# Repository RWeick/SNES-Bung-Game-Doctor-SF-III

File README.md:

# SNES-Bung-Game-Doctor-SF-III
The mainboard and memory board addon Kicad files for the Bung Game Doctor SF III. 

There were two bodged capacitors, 30 pF and 100 pF, that I've added footprints for on the PCB. I have also added a PLCC-32 footprint for the ROM. Everything else is original.

Mainboard PCB Thickness: 1.6 mm
RAM PCB Thicknesses: 1.2 mm

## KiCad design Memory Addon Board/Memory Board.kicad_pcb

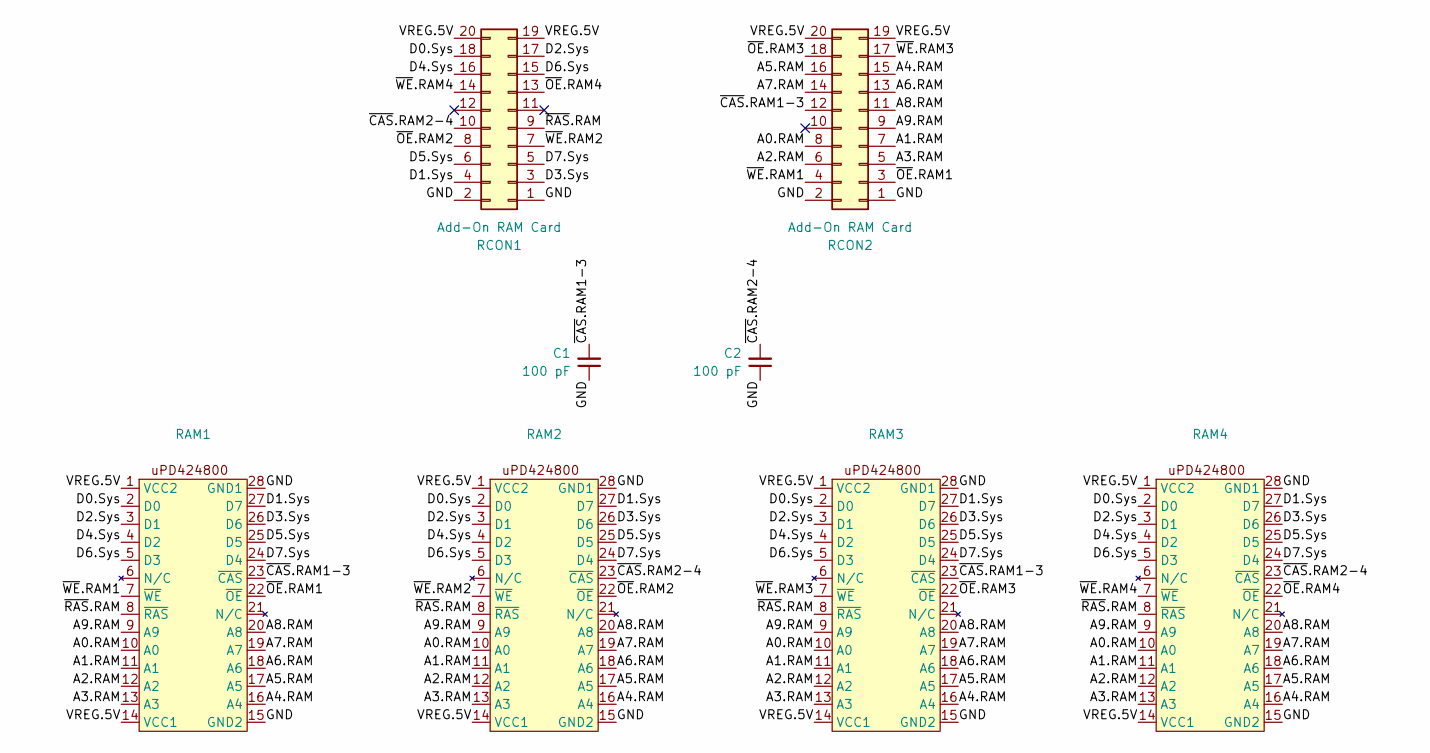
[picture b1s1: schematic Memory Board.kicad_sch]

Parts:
C1, C2: 100 pF; SMD Passive
RAM1, RAM2, RAM3, RAM4: uPD424800
RCON1, RCON2: Add-On RAM Card; PinHeader_2x10_P2.54mm_Vertical

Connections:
/A0.RAM: RAM1.10 (A0), RAM2.10 (A0), RAM3.10 (A0), RAM4.10 (A0), RCON2.8
/A1.RAM: RAM1.11 (A1), RAM2.11 (A1), RAM3.11 (A1), RAM4.11 (A1), RCON2.7
/A2.RAM: RAM1.12 (A2), RAM2.12 (A2), RAM3.12 (A2), RAM4.12 (A2), RCON2.6
/A3.RAM: RAM1.13 (A3), RAM2.13 (A3), RAM3.13 (A3), RAM4.13 (A3), RCON2.5
/A4.RAM: RAM1.16 (A4), RAM2.16 (A4), RAM3.16 (A4), RAM4.16 (A4), RCON2.15
/A5.RAM: RAM1.17 (A5), RAM2.17 (A5), RAM3.17 (A5), RAM4.17 (A5), RCON2.16
/A6.RAM: RAM1.18 (A6), RAM2.18 (A6), RAM3.18 (A6), RAM4.18 (A6), RCON2.13
/A7.RAM: RAM1.19 (A7), RAM2.19 (A7), RAM3.19 (A7), RAM4.19 (A7), RCON2.14
/A8.RAM: RAM1.20 (A8), RAM2.20 (A8), RAM3.20 (A8), RAM4.20 (A8), RCON2.11
/A9.RAM: RAM1.9 (A9), RAM2.9 (A9), RAM3.9 (A9), RAM4.9 (A9), RCON2.9
/D0.Sys: RAM1.2 (D0), RAM2.2 (D0), RAM3.2 (D0), RAM4.2 (D0), RCON1.18
/D1.Sys: RAM1.27 (D7), RAM2.27 (D7), RAM3.27 (D7), RAM4.27 (D7), RCON1.4
/D2.Sys: RAM1.3 (D1), RAM2.3 (D1), RAM3.3 (D1), RAM4.3 (D1), RCON1.17
/D3.Sys: RAM1.26 (D6), RAM2.26 (D6), RAM3.26 (D6), RAM4.26 (D6), RCON1.3
/D4.Sys: RAM1.4 (D2), RAM2.4 (D2), RAM3.4 (D2), RAM4.4 (D2), RCON1.16
/D5.Sys: RAM1.25 (D5), RAM2.25 (D5), RAM3.25 (D5), RAM4.25 (D5), RCON1.6
/D6.Sys: RAM1.5 (D3), RAM2.5 (D3), RAM3.5 (D3), RAM4.5 (D3), RCON1.15
/D7.Sys: RAM1.24 (D4), RAM2.24 (D4), RAM3.24 (D4), RAM4.24 (D4), RCON1.5
/GND: C1.1, C2.1, RAM1.15 (GND2), RAM1.28 (GND1), RAM2.15 (GND2), RAM2.28 (GND1), RAM3.15 (GND2), RAM3.28 (GND1), RAM4.15 (GND2), RAM4.28 (GND1), RCON1.1, RCON1.2, RCON2.1, RCON2.2
/VREG.5V: RAM1.1 (VCC2), RAM1.14 (VCC1), RAM2.1 (VCC2), RAM2.14 (VCC1), RAM3.1 (VCC2), RAM3.14 (VCC1), RAM4.1 (VCC2), RAM4.14 (VCC1), RCON1.19, RCON1.20, RCON2.19, RCON2.20
/~CAS.RAM1-3: C1.2, RAM1.23 (~CAS), RAM3.23 (~CAS), RCON2.12
/~CAS.RAM2-4: C2.2, RAM2.23 (~CAS), RAM4.23 (~CAS), RCON1.10
/~OE.RAM1: RAM1.22 (~OE), RCON2.3
/~OE.RAM2: RAM2.22 (~OE), RCON1.8
/~OE.RAM3: RAM3.22 (~OE), RCON2.18
/~OE.RAM4: RAM4.22 (~OE), RCON1.13
/~RAS.RAM: RAM1.8 (~RAS), RAM2.8 (~RAS), RAM3.8 (~RAS), RAM4.8 (~RAS), RCON1.9
/~WE.RAM1: RAM1.7 (~WE), RCON2.4
/~WE.RAM2: RAM2.7 (~WE), RCON1.7
/~WE.RAM3: RAM3.7 (~WE), RCON2.17
/~WE.RAM4: RAM4.7 (~WE), RCON1.14

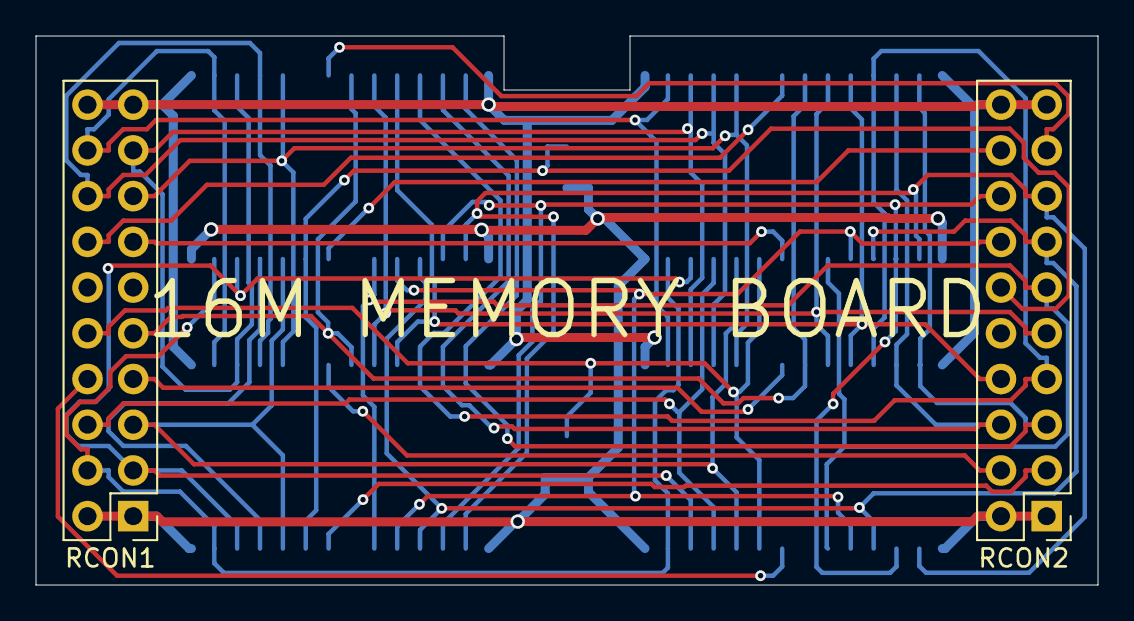
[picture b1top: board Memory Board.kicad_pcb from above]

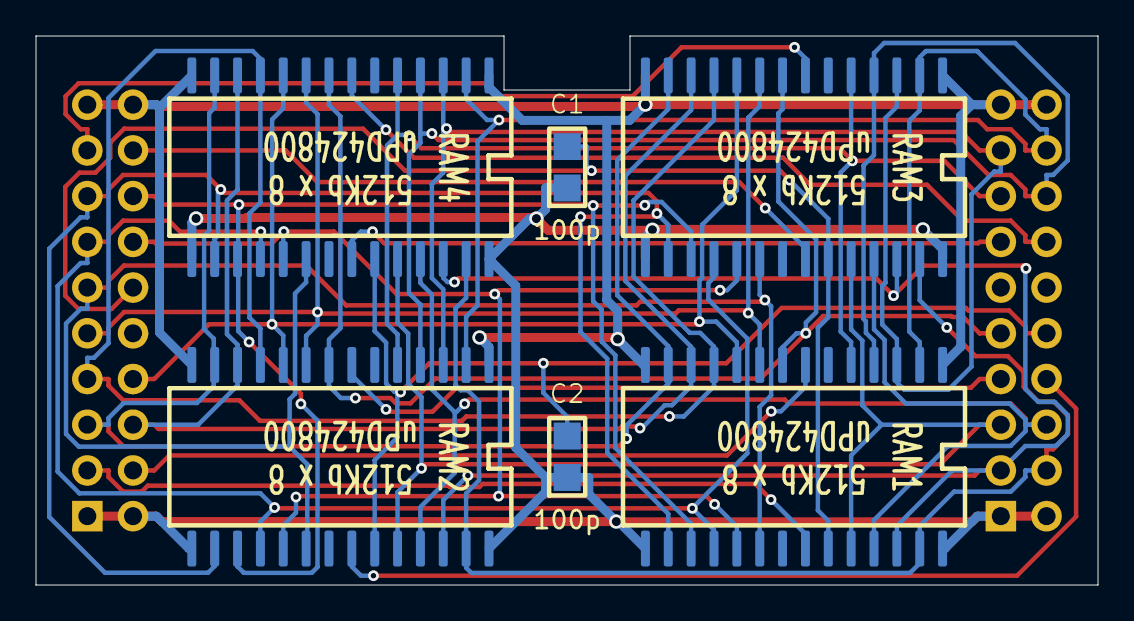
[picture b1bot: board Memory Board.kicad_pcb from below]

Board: 2 copper layers, 59.0 x 30.5 mm, 8 parts (6 on the bottom side), 31 nets.

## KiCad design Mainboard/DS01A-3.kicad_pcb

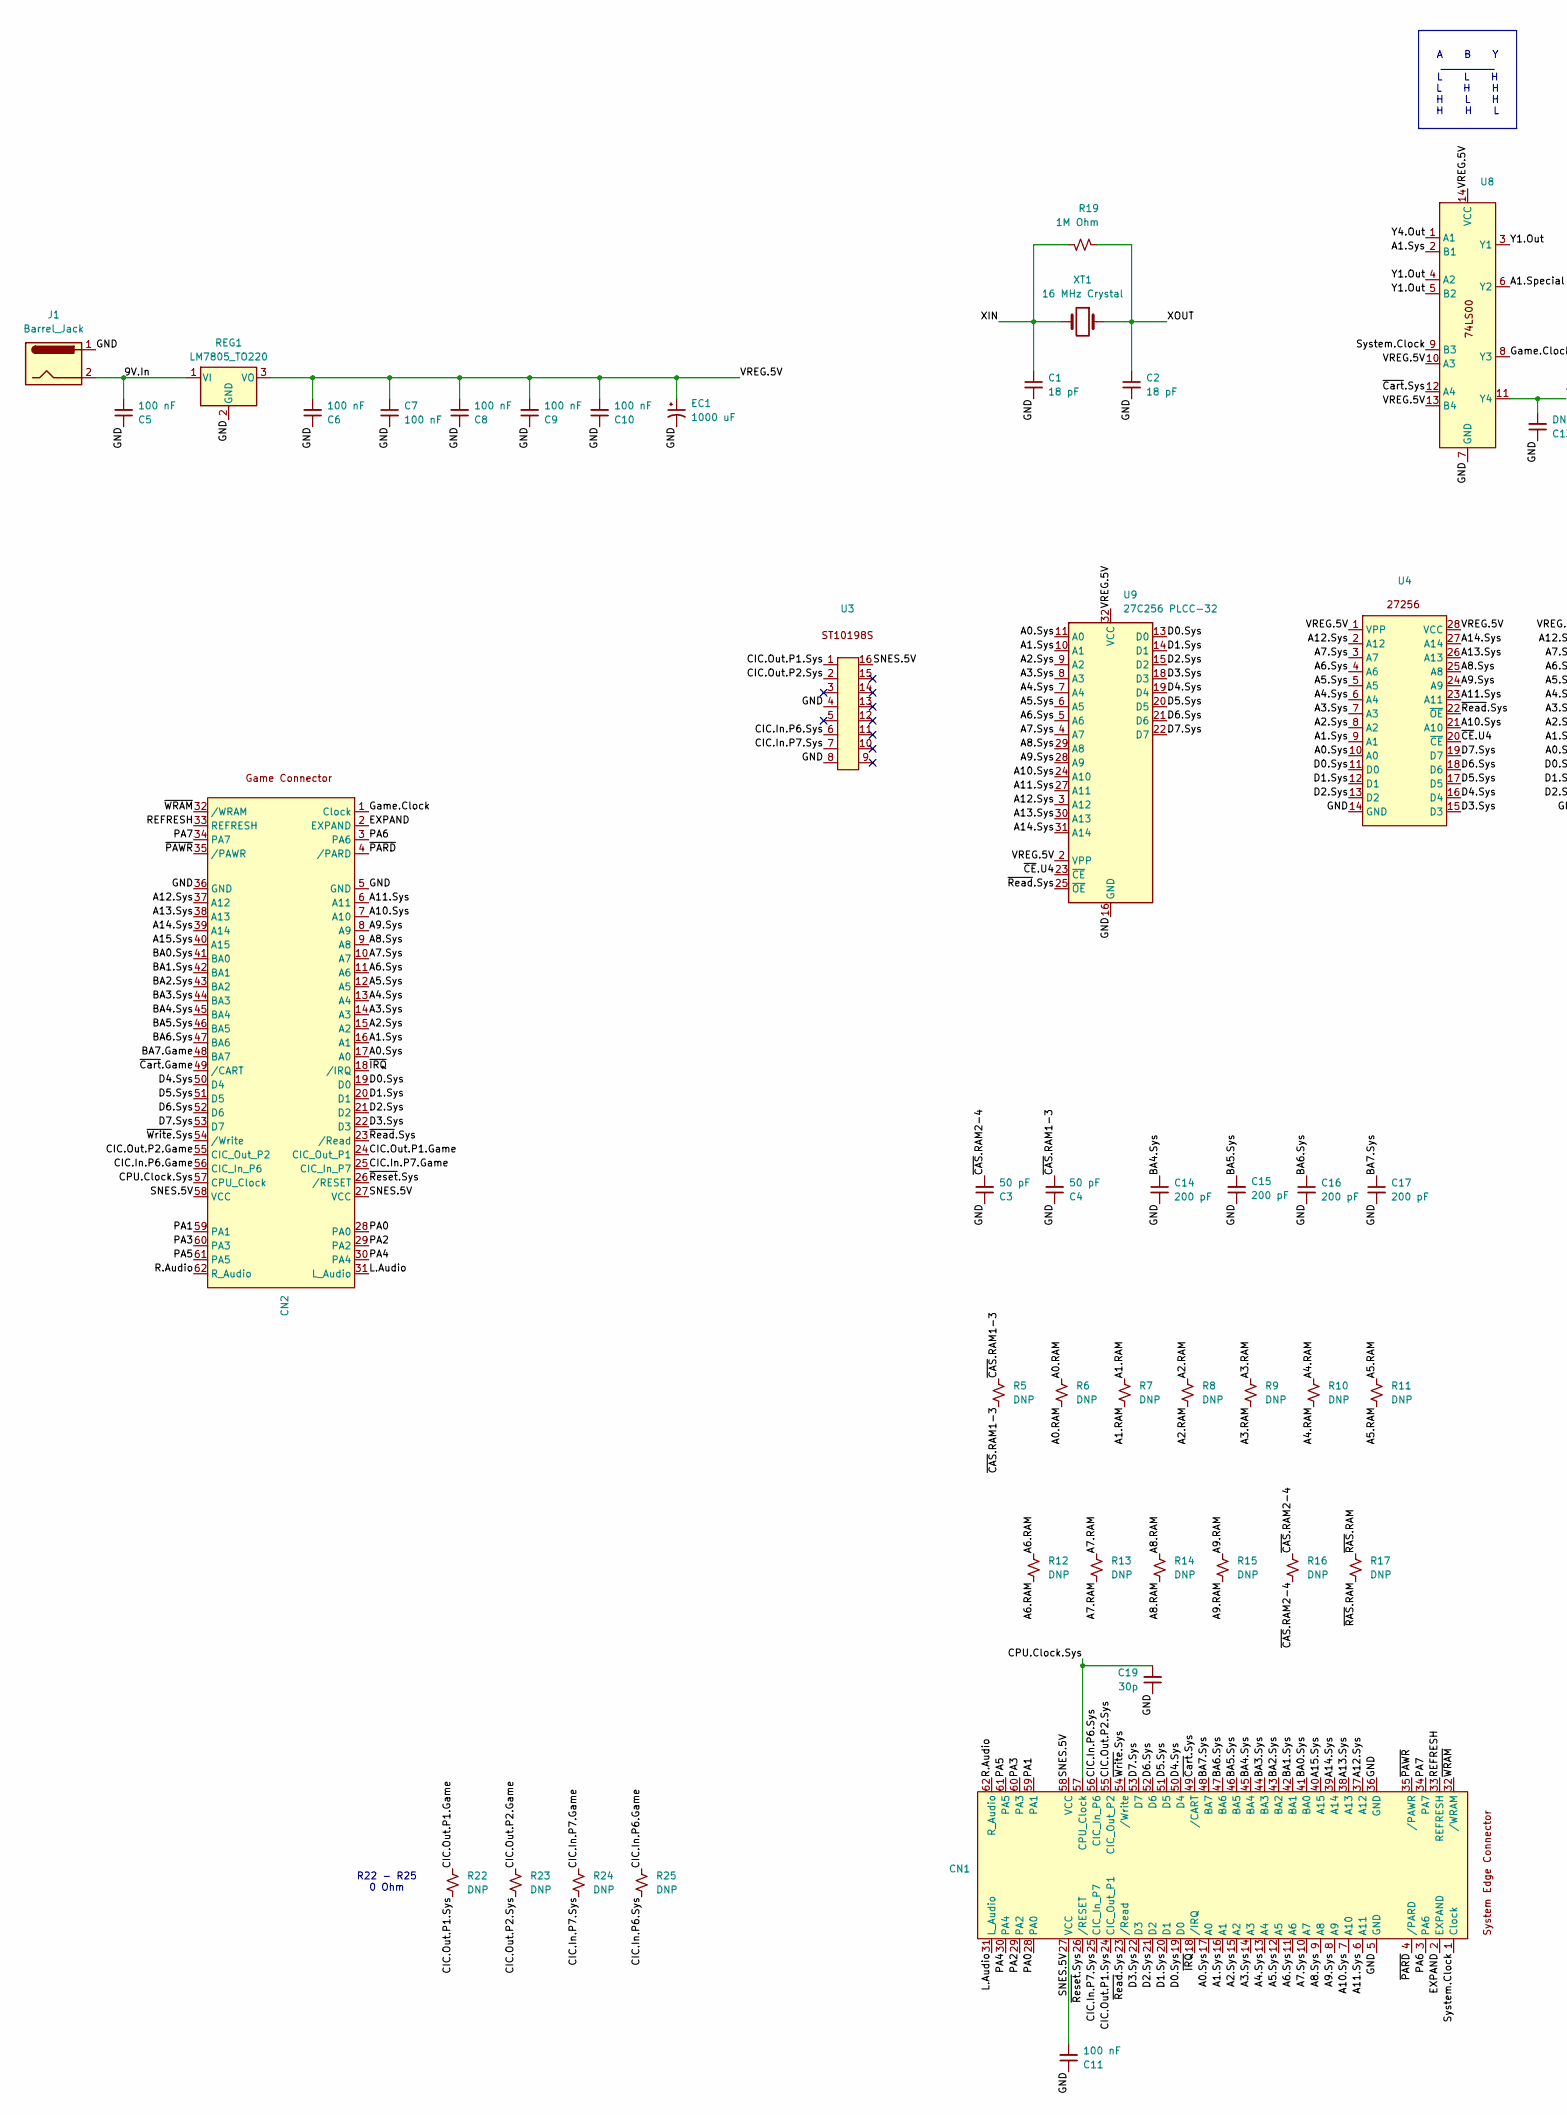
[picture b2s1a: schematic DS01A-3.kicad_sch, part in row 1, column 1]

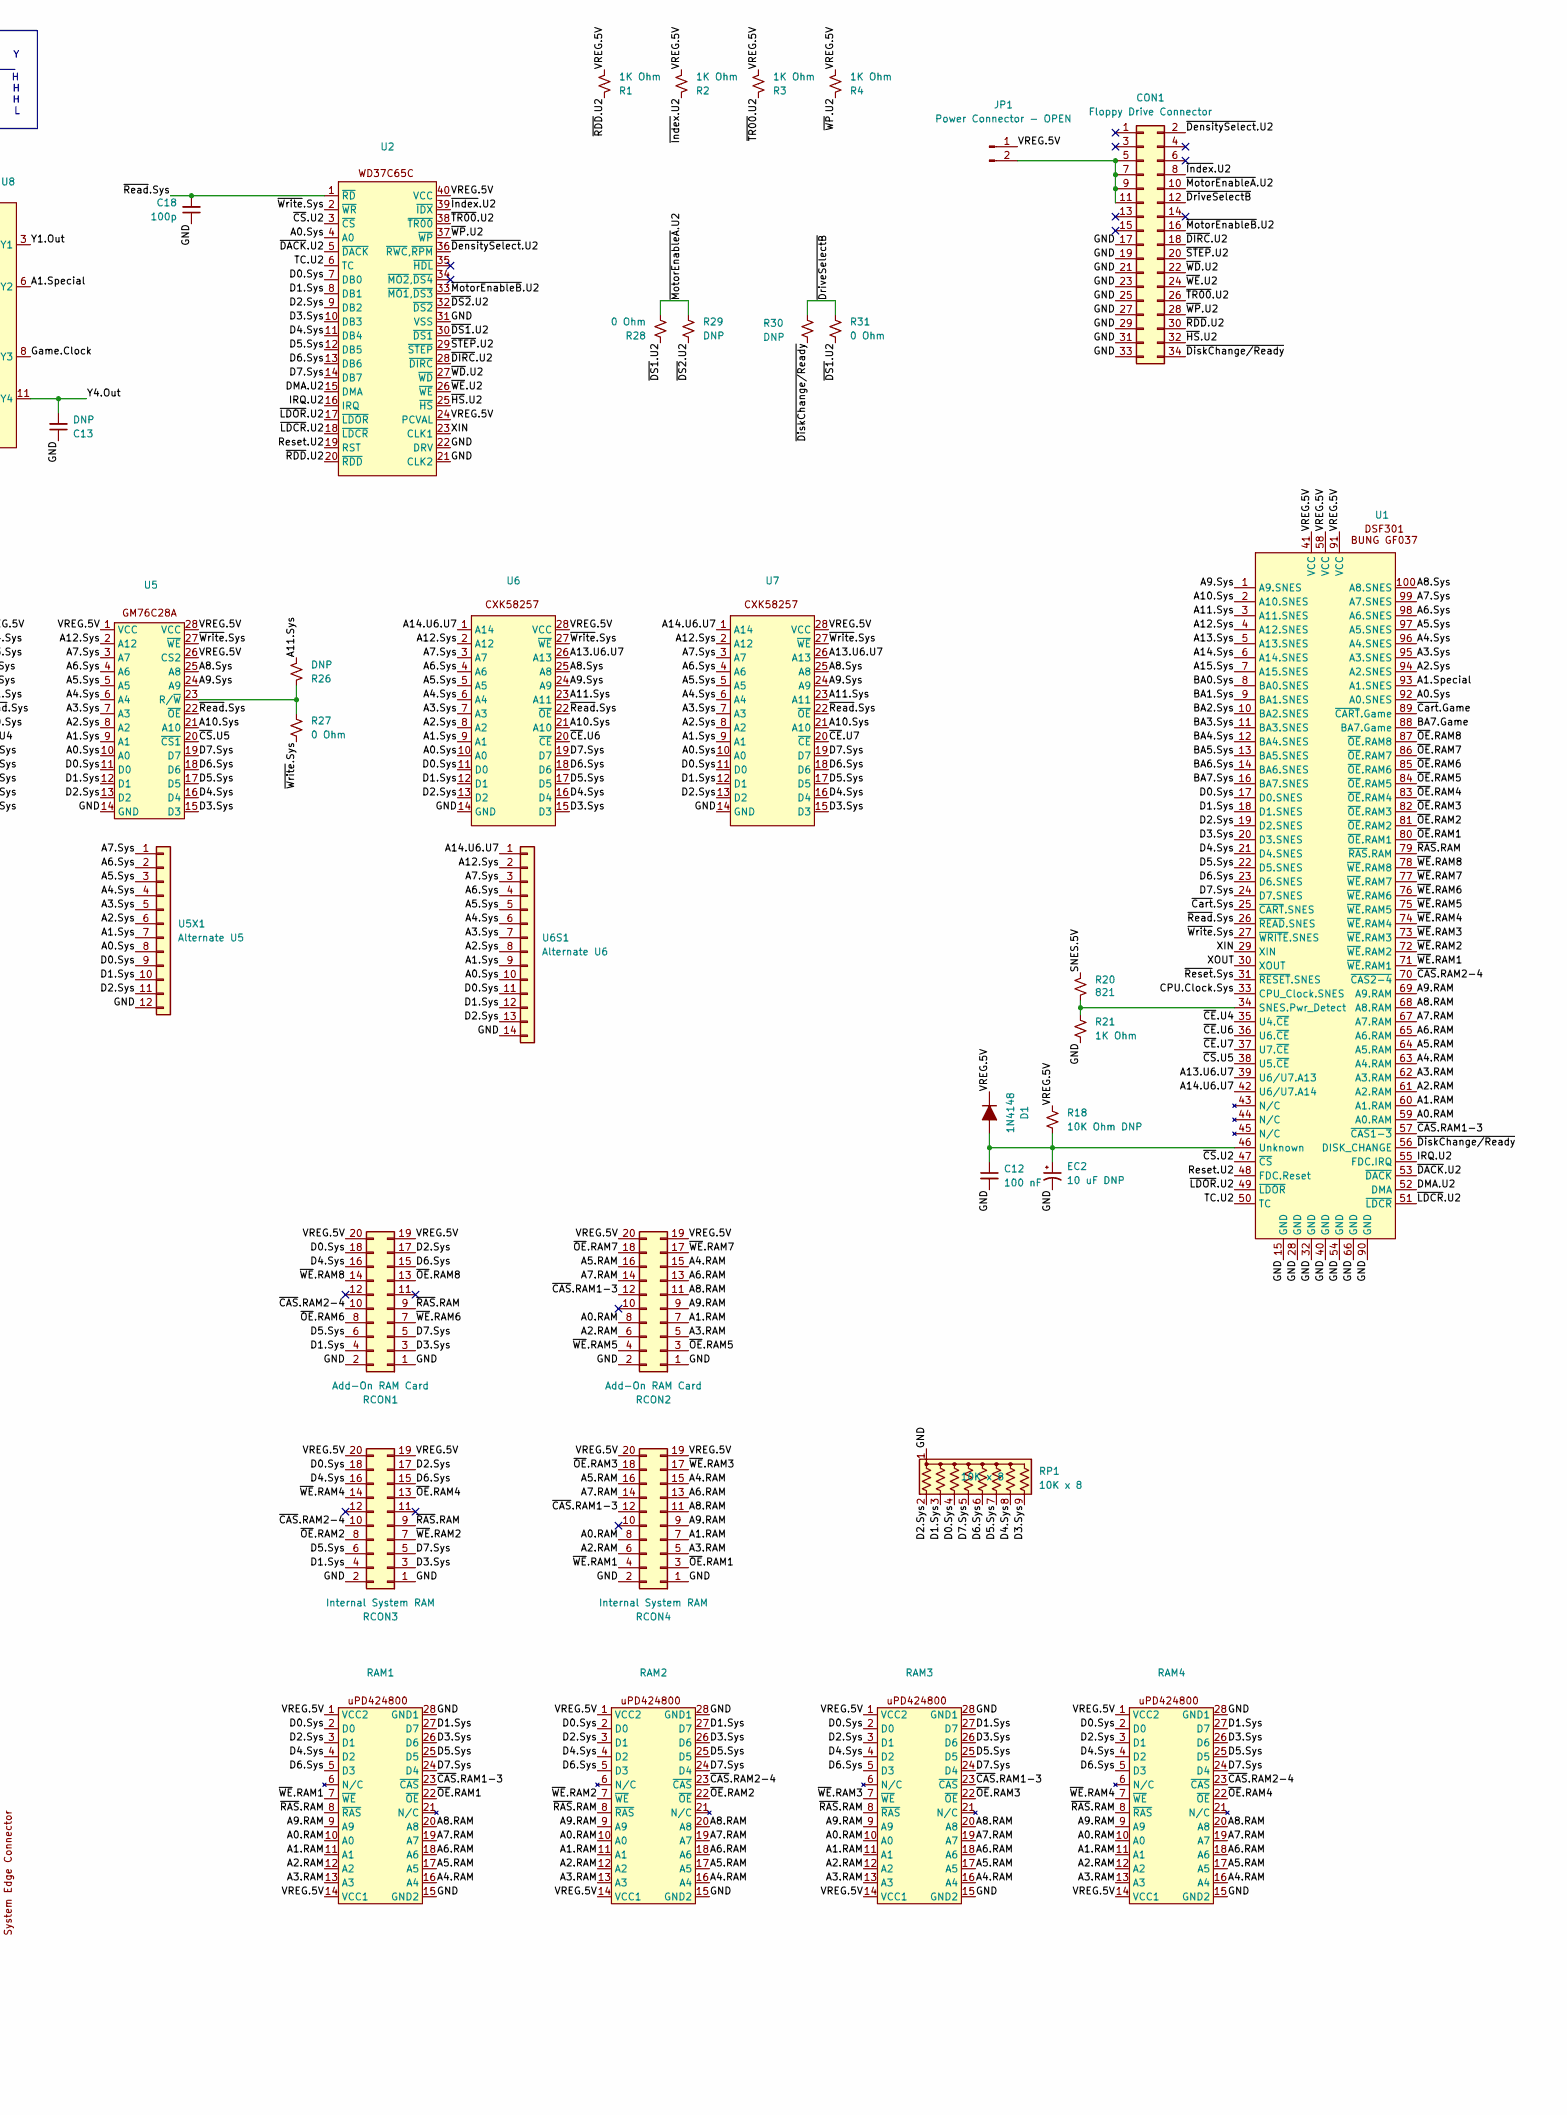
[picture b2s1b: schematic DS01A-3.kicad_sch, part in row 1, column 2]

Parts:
C1, C2: 18 pF; SMD Passive
C3, C4: 50 pF; SMD Passive
C5, C6, C7, C8, C9, C10, C11, C12: 100 nF; SMD Passive
C13: DNP; SMD Passive
C14, C15, C16, C17: 200 pF; SMD Passive
C18: 100p; SMD Passive
C19: 30p; SMD Passive
CN1, CN2: Cartridge Slot
CON1: Floppy Drive Connector; PinHeader_2x17_P2.54mm_Vertical
D1: 1N4148; Diode
EC1: 1000 uF; CP_Radial_D8.0mm_P3.50mm
EC2: 10 uF DNP; EC2
J1: Barrel_Jack; DC Jack
JP1: Power Connector - OPEN; PinHeader_1x02_P2.54mm_Vertical
R1, R2, R3, R4, R21: 1K Ohm; SMD Passive
R5, R6, R7, R8, R9, R10, R11, R12, R13, R14, R15, R16, R17, R22, R23, R24, R25, R26, R29, R30: DNP; SMD Passive
R18: 10K Ohm DNP; SMD Passive
R19: 1M Ohm; SMD Passive
R20: 821; SMD Passive
R27, R28, R31: 0 Ohm; SMD Passive
RAM1, RAM2, RAM3, RAM4: uPD424800
RCON1, RCON2: Add-On RAM Card; PinHeader_2x10_P2.54mm_Vertical
RCON3, RCON4: Internal System RAM; PinHeader_2x10_P2.54mm_Vertical
REG1: LM7805_TO220; TO-220-3_Horizontal_TabDown
RP1: 10K x 8; R_Array_SIP9
U1: ASIC DS01
U2: DIP-40_W15.24mm
U3: DIP-16_W7.62mm
U4, U5, U6, U7: DIP-28_W15.24mm
U5X1: Alternate U5; DIP-24_W7.62mm
U6S1: Alternate U6; DIP-28_W7.62mm
U8: DIP-14_W7.62mm
U9: 27C256 PLCC-32; PLCC-32_11.4x14.0mm_P1.27mm
XT1: 16 MHz Crystal; Crystal

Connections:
/9V.In: C5.2, J1.2, REG1.1 (VI)
/A0.RAM: R6.1, R6.2, RAM1.10 (A0), RAM2.10 (A0), RAM3.10 (A0), RAM4.10 (A0), RCON2.8, RCON4.8, U1.59 (A0.RAM)
/A0.Sys: CN1.17 (A0), CN2.17 (A0), U1.92 (A0.SNES), U2.4 (A0), U4.10 (A0), U5.10 (A0), U5X1.8, U6.10 (A0), U6S1.10, U7.10 (A0), U9.11 (A0)
/A1.RAM: R7.1, R7.2, RAM1.11 (A1), RAM2.11 (A1), RAM3.11 (A1), RAM4.11 (A1), RCON2.7, RCON4.7, U1.60 (A1.RAM)
/A1.Special: U1.93 (A1.SNES), U8.6 (Y2)
/A1.Sys: CN1.16 (A1), CN2.16 (A1), U4.9 (A1), U5.9 (A1), U5X1.7, U6.9 (A1), U6S1.9, U7.9 (A1), U8.2 (B1), U9.10 (A1)
/A2.RAM: R8.1, R8.2, RAM1.12 (A2), RAM2.12 (A2), RAM3.12 (A2), RAM4.12 (A2), RCON2.6, RCON4.6, U1.61 (A2.RAM)
/A2.Sys: CN1.15 (A2), CN2.15 (A2), U1.94 (A2.SNES), U4.8 (A2), U5.8 (A2), U5X1.6, U6.8 (A2), U6S1.8, U7.8 (A2), U9.9 (A2)
/A3.RAM: R9.1, R9.2, RAM1.13 (A3), RAM2.13 (A3), RAM3.13 (A3), RAM4.13 (A3), RCON2.5, RCON4.5, U1.62 (A3.RAM)
/A3.Sys: CN1.14 (A3), CN2.14 (A3), U1.95 (A3.SNES), U4.7 (A3), U5.7 (A3), U5X1.5, U6.7 (A3), U6S1.7, U7.7 (A3), U9.8 (A3)
/A4.RAM: R10.1, R10.2, RAM1.16 (A4), RAM2.16 (A4), RAM3.16 (A4), RAM4.16 (A4), RCON2.15, RCON4.15, U1.63 (A4.RAM)
/A4.Sys: CN1.13 (A4), CN2.13 (A4), U1.96 (A4.SNES), U4.6 (A4), U5.6 (A4), U5X1.4, U6.6 (A4), U6S1.6, U7.6 (A4), U9.7 (A4)
/A5.RAM: R11.1, R11.2, RAM1.17 (A5), RAM2.17 (A5), RAM3.17 (A5), RAM4.17 (A5), RCON2.16, RCON4.16, U1.64 (A5.RAM)
/A5.Sys: CN1.12 (A5), CN2.12 (A5), U1.97 (A5.SNES), U4.5 (A5), U5.5 (A5), U5X1.3, U6.5 (A5), U6S1.5, U7.5 (A5), U9.6 (A5)
/A6.RAM: R12.1, R12.2, RAM1.18 (A6), RAM2.18 (A6), RAM3.18 (A6), RAM4.18 (A6), RCON2.13, RCON4.13, U1.65 (A6.RAM)
/A6.Sys: CN1.11 (A6), CN2.11 (A6), U1.98 (A6.SNES), U4.4 (A6), U5.4 (A6), U5X1.2, U6.4 (A6), U6S1.4, U7.4 (A6), U9.5 (A6)
/A7.RAM: R13.1, R13.2, RAM1.19 (A7), RAM2.19 (A7), RAM3.19 (A7), RAM4.19 (A7), RCON2.14, RCON4.14, U1.67 (A7.RAM)
/A7.Sys: CN1.10 (A7), CN2.10 (A7), U1.99 (A7.SNES), U4.3 (A7), U5.3 (A7), U5X1.1, U6.3 (A7), U6S1.3, U7.3 (A7), U9.4 (A7)
/A8.RAM: R14.1, R14.2, RAM1.20 (A8), RAM2.20 (A8), RAM3.20 (A8), RAM4.20 (A8), RCON2.11, RCON4.11, U1.68 (A8.RAM)
/A8.Sys: CN1.9 (A8), CN2.9 (A8), U1.100 (A8.SNES), U4.25 (A8), U5.25 (A8), U6.25 (A8), U7.25 (A8), U9.29 (A8)
/A9.RAM: R15.1, R15.2, RAM1.9 (A9), RAM2.9 (A9), RAM3.9 (A9), RAM4.9 (A9), RCON2.9, RCON4.9, U1.69 (A9.RAM)
/A9.Sys: CN1.8 (A9), CN2.8 (A9), U1.1 (A9.SNES), U4.24 (A9), U5.24 (A9), U6.24 (A9), U7.24 (A9), U9.28 (A9)
/A10.Sys: CN1.7 (A10), CN2.7 (A10), U1.2 (A10.SNES), U4.21 (A10), U5.21 (A10), U6.21 (A10), U7.21 (A10), U9.24 (A10)
/A11.Sys: CN1.6 (A11), CN2.6 (A11), R26.2, U1.3 (A11.SNES), U4.23 (A11), U6.23 (A11), U7.23 (A11), U9.27 (A11)
/A12.Sys: CN1.37 (A12), CN2.37 (A12), U1.4 (A12.SNES), U4.2 (A12), U5.2 (A12), U6.2 (A12), U6S1.2, U7.2 (A12), U9.3 (A12)
/A13.Sys: CN1.38 (A13), CN2.38 (A13), U1.5 (A13.SNES), U4.26 (A13), U9.30 (A13)
/A13.U6.U7: U1.39 (U6/U7.A13), U6.26 (A13), U7.26 (A13)
/A14.Sys: CN1.39 (A14), CN2.39 (A14), U1.6 (A14.SNES), U4.27 (A14), U9.31 (A14)
/A14.U6.U7: U1.42 (U6/U7.A14), U6.1 (A14), U6S1.1, U7.1 (A14)
/A15.Sys: CN1.40 (A15), CN2.40 (A15), U1.7 (A15.SNES)
/BA0.Sys: CN1.41 (BA0), CN2.41 (BA0), U1.8 (BA0.SNES)
/BA1.Sys: CN1.42 (BA1), CN2.42 (BA1), U1.9 (BA1.SNES)
/BA2.Sys: CN1.43 (BA2), CN2.43 (BA2), U1.10 (BA2.SNES)
/BA3.Sys: CN1.44 (BA3), CN2.44 (BA3), U1.11 (BA3.SNES)
/BA4.Sys: C14.1, CN1.45 (BA4), CN2.45 (BA4), U1.12 (BA4.SNES)
/BA5.Sys: C15.2, CN1.46 (BA5), CN2.46 (BA5), U1.13 (BA5.SNES)
/BA6.Sys: C16.1, CN1.47 (BA6), CN2.47 (BA6), U1.14 (BA6.SNES)
/BA7.Game: CN2.48 (BA7), U1.88 (BA7.Game)
/BA7.Sys: C17.1, CN1.48 (BA7), U1.16 (BA7.SNES)
/CIC.In.P6.Game: CN2.56 (CIC_In_P6), R25.1
/CIC.In.P6.Sys: CN1.56 (CIC_In_P6), R25.2, U3.6
/CIC.In.P7.Game: CN2.25 (CIC_In_P7), R24.1
/CIC.In.P7.Sys: CN1.25 (CIC_In_P7), R24.2, U3.7
/CIC.Out.P1.Game: CN2.24 (CIC_Out_P1), R22.1
/CIC.Out.P1.Sys: CN1.24 (CIC_Out_P1), R22.2, U3.1
/CIC.Out.P2.Game: CN2.55 (CIC_Out_P2), R23.1
/CIC.Out.P2.Sys: CN1.55 (CIC_Out_P2), R23.2, U3.2
/CPU.Clock.Sys: C19.2, CN1.57 (CPU_Clock), CN2.57 (CPU_Clock), U1.33 (CPU_Clock.SNES)
/D0.Sys: CN1.19 (D0), CN2.19 (D0), RAM1.2 (D0), RAM2.2 (D0), RAM3.2 (D0), RAM4.2 (D0), RCON1.18, RCON3.18, RP1.4 (R3), U1.17 (D0.SNES), U2.7 (DB0), U4.11 (D0), U5.11 (D0), U5X1.9, U6.11 (D0), U6S1.11, U7.11 (D0), U9.13 (D0)
/D1.Sys: CN1.20 (D1), CN2.20 (D1), RAM1.27 (D7), RAM2.27 (D7), RAM3.27 (D7), RAM4.27 (D7), RCON1.4, RCON3.4, RP1.3 (R2), U1.18 (D1.SNES), U2.8 (DB1), U4.12 (D1), U5.12 (D1), U5X1.10, U6.12 (D1), U6S1.12, U7.12 (D1), U9.14 (D1)
/D2.Sys: CN1.21 (D2), CN2.21 (D2), RAM1.3 (D1), RAM2.3 (D1), RAM3.3 (D1), RAM4.3 (D1), RCON1.17, RCON3.17, RP1.2 (R1), U1.19 (D2.SNES), U2.9 (DB2), U4.13 (D2), U5.13 (D2), U5X1.11, U6.13 (D2), U6S1.13, U7.13 (D2), U9.15 (D2)
/D3.Sys: CN1.22 (D3), CN2.22 (D3), RAM1.26 (D6), RAM2.26 (D6), RAM3.26 (D6), RAM4.26 (D6), RCON1.3, RCON3.3, RP1.9 (R8), U1.20 (D3.SNES), U2.10 (DB3), U4.15 (D3), U5.15 (D3), U6.15 (D3), U7.15 (D3), U9.18 (D3)
/D4.Sys: CN1.50 (D4), CN2.50 (D4), RAM1.4 (D2), RAM2.4 (D2), RAM3.4 (D2), RAM4.4 (D2), RCON1.16, RCON3.16, RP1.8 (R7), U1.21 (D4.SNES), U2.11 (DB4), U4.16 (D4), U5.16 (D4), U6.16 (D4), U7.16 (D4), U9.19 (D4)
/D5.Sys: CN1.51 (D5), CN2.51 (D5), RAM1.25 (D5), RAM2.25 (D5), RAM3.25 (D5), RAM4.25 (D5), RCON1.6, RCON3.6, RP1.7 (R6), U1.22 (D5.SNES), U2.12 (DB5), U4.17 (D5), U5.17 (D5), U6.17 (D5), U7.17 (D5), U9.20 (D5)
/D6.Sys: CN1.52 (D6), CN2.52 (D6), RAM1.5 (D3), RAM2.5 (D3), RAM3.5 (D3), RAM4.5 (D3), RCON1.15, RCON3.15, RP1.6 (R5), U1.23 (D6.SNES), U2.13 (DB6), U4.18 (D6), U5.18 (D6), U6.18 (D6), U7.18 (D6), U9.21 (D6)
/D7.Sys: CN1.53 (D7), CN2.53 (D7), RAM1.24 (D4), RAM2.24 (D4), RAM3.24 (D4), RAM4.24 (D4), RCON1.5, RCON3.5, RP1.5 (R4), U1.24 (D7.SNES), U2.14 (DB7), U4.19 (D7), U5.19 (D7), U6.19 (D7), U7.19 (D7), U9.22 (D7)
/DMA.U2: U1.52 (DMA), U2.15 (DMA)
/EXPAND: CN1.2 (EXPAND), CN2.2 (EXPAND)
/GND: C1.2, C2.2, C3.1, C4.1, C5.1, C6.1, C7.2, C8.1, C9.1, C10.1, C11.1, C12.2, C13.1, C14.2, C15.1, C16.2, C17.2, C18.1, C19.1, CN1.5 (GND), CN1.36 (GND), CN2.5 (GND), CN2.36 (GND), CON1.17, CON1.19, CON1.21, CON1.23, CON1.25, CON1.27, CON1.29, CON1.31, CON1.33, EC1.2, EC2.2, J1.1, R21.2, RAM1.15 (GND2), RAM1.28 (GND1), RAM2.15 (GND2), RAM2.28 (GND1), RAM3.15 (GND2), RAM3.28 (GND1), RAM4.15 (GND2), RAM4.28 (GND1), RCON1.1, RCON1.2, RCON2.1, RCON2.2, RCON3.1, RCON3.2, RCON4.1, RCON4.2, REG1.2 (GND), RP1.1 (common), U1.15 (GND), U1.28 (GND), U1.32 (GND), U1.40 (GND), U1.54 (GND), U1.66 (GND), U1.90 (GND), U2.21 (CLK2), U2.22 (DRV), U2.31 (VSS), U3.4, U3.8, U4.14 (GND), U5.14 (GND), U5X1.12, U6.14 (GND), U6S1.14, U7.14 (GND), U8.7 (GND), U9.16 (GND)
/Game.Clock: CN2.1 (Clock), U8.8 (Y3)
/IRQ.U2: U1.55 (FDC.IRQ), U2.16 (IRQ)
/L.Audio: CN1.31 (L_Audio), CN2.31 (L_Audio)
/PA0: CN1.28 (PA0), CN2.28 (PA0)
/PA1: CN1.59 (PA1), CN2.59 (PA1)
/PA2: CN1.29 (PA2), CN2.29 (PA2)
/PA3: CN1.60 (PA3), CN2.60 (PA3)
/PA4: CN1.30 (PA4), CN2.30 (PA4)
/PA5: CN1.61 (PA5), CN2.61 (PA5)
/PA6: CN1.3 (PA6), CN2.3 (PA6)
/PA7: CN1.34 (PA7), CN2.34 (PA7)
/R.Audio: CN1.62 (R_Audio), CN2.62 (R_Audio)
/REFRESH: CN1.33 (REFRESH), CN2.33 (REFRESH)
/Reset.U2: U1.48 (FDC.Reset), U2.19 (RST)
/SNES.5V: C11.2, CN1.27 (VCC), CN1.58 (VCC), CN2.27 (VCC), CN2.58 (VCC), R20.2, U3.16
/System.Clock: CN1.1 (Clock), U8.9 (B3)
/TC.U2: U1.50 (TC), U2.6 (TC)
/VREG.5V: C6.2, C7.1, C8.2, C9.2, C10.2, D1.1 (K), EC1.1, JP1.1, R1.2, R2.2, R3.2, R4.2, R18.1, RAM1.1 (VCC2), RAM1.14 (VCC1), RAM2.1 (VCC2), RAM2.14 (VCC1), RAM3.1 (VCC2), RAM3.14 (VCC1), RAM4.1 (VCC2), RAM4.14 (VCC1), RCON1.19, RCON1.20, RCON2.19, RCON2.20, RCON3.19, RCON3.20, RCON4.19, RCON4.20, REG1.3 (VO), U1.41 (VCC), U1.58 (VCC), U1.91 (VCC), U2.24 (PCVAL), U2.40 (VCC), U4.1 (VPP), U4.28 (VCC), U5.1 (VCC), U5.26 (CS2), U5.28 (VCC), U6.28 (VCC), U7.28 (VCC), U8.10 (A3), U8.13 (B4), U8.14 (VCC), U9.2 (VPP), U9.32 (VCC)
/XIN: C1.1, R19.1, U1.29 (XIN), U2.23 (CLK1), XT1.2
/XOUT: C2.1, R19.2, U1.30 (XOUT), XT1.1
/Y1.Out: U8.3 (Y1), U8.4 (A2), U8.5 (B2)
/Y4.Out: C13.2, U8.1 (A1), U8.11 (Y4)
/~CAS.RAM1-3: C4.2, R5.1, R5.2, RAM1.23 (~CAS), RAM3.23 (~CAS), RCON2.12, RCON4.12, U1.57 (~CAS1-3)
/~CAS.RAM2-4: C3.2, R16.1, R16.2, RAM2.23 (~CAS), RAM4.23 (~CAS), RCON1.10, RCON3.10, U1.70 (~CAS2-4)
/~CE.U4: U1.35 (U4.~CE), U4.20 (~CE), U9.23 (~CE)
/~CE.U6: U1.36 (U6.~CE), U6.20 (~CE)
/~CE.U7: U1.37 (U7.~CE), U7.20 (~CE)
/~CS.U2: U1.47 (~CS), U2.3 (~CS)
/~CS.U5: U1.38 (U5.~CE), U5.20 (~CS1)
/~Cart.Game: CN2.49 (/CART), U1.89 (~CART.Game)
/~Cart.Sys: CN1.49 (/CART), U1.25 (~CART.SNES), U8.12 (A4)
/~DACK.U2: U1.53 (~DACK), U2.5 (~DACK)
/~DIRC.U2: CON1.18, U2.28 (~DIRC)
/~DS1.U2: R28.1, R31.2, U2.30 (~DS1)
/~DS2.U2: R29.2, U2.32 (~DS2)
/~DensitySelect.U2: CON1.2, U2.36 (~RWC,~RPM)
/~DiskChange/Ready: CON1.34, R30.1, U1.56 (DISK_CHANGE)
/~DriveSelectB: CON1.12, R30.2, R31.1
/~HS.U2: CON1.32, U2.25 (~HS)
/~IRQ: CN1.18 (/IRQ), CN2.18 (/IRQ)
/~Index.U2: CON1.8, R2.1, U2.39 (~IDX)
/~LDCR.U2: U1.51 (~LDCR), U2.18 (~LDCR)
/~LDOR.U2: U1.49 (~LDOR), U2.17 (~LDOR)
/~MotorEnableA.U2: CON1.10, R28.2, R29.1
/~MotorEnableB.U2: CON1.16, U2.33 (~MO1,~DS3)
/~OE.RAM1: RAM1.22 (~OE), RCON4.3, U1.80 (~OE.RAM1)
/~OE.RAM2: RAM2.22 (~OE), RCON3.8, U1.81 (~OE.RAM2)
/~OE.RAM3: RAM3.22 (~OE), RCON4.18, U1.82 (~OE.RAM3)
/~OE.RAM4: RAM4.22 (~OE), RCON3.13, U1.83 (~OE.RAM4)
/~OE.RAM5: RCON2.3, U1.84 (~OE.RAM5)
/~OE.RAM6: RCON1.8, U1.85 (~OE.RAM6)
/~OE.RAM7: RCON2.18, U1.86 (~OE.RAM7)
/~OE.RAM8: RCON1.13, U1.87 (~OE.RAM8)
/~PARD: CN1.4 (/PARD), CN2.4 (/PARD)
/~PAWR: CN1.35 (/PAWR), CN2.35 (/PAWR)
/~RAS.RAM: R17.1, R17.2, RAM1.8 (~RAS), RAM2.8 (~RAS), RAM3.8 (~RAS), RAM4.8 (~RAS), RCON1.9, RCON3.9, U1.79 (~RAS.RAM)
/~RDD.U2: CON1.30, R1.1, U2.20 (~RDD)
/~Read.Sys: C18.2, CN1.23 (/Read), CN2.23 (/Read), U1.26 (~READ.SNES), U2.1 (~RD), U4.22 (~OE), U5.22 (~OE), U6.22 (~OE), U7.22 (~OE), U9.25 (~OE)
/~Reset.Sys: CN1.26 (/RESET), CN2.26 (/RESET), U1.31 (~RESET.SNES)
/~STEP.U2: CON1.20, U2.29 (~STEP)
/~TR00.U2: CON1.26, R3.1, U2.38 (~TR00)
/~WD.U2: CON1.22, U2.27 (~WD)
/~WE.RAM1: RAM1.7 (~WE), RCON4.4, U1.71 (~WE.RAM1)
/~WE.RAM2: RAM2.7 (~WE), RCON3.7, U1.72 (~WE.RAM2)
/~WE.RAM3: RAM3.7 (~WE), RCON4.17, U1.73 (~WE.RAM3)
/~WE.RAM4: RAM4.7 (~WE), RCON3.14, U1.74 (~WE.RAM4)
/~WE.RAM5: RCON2.4, U1.75 (~WE.RAM5)
/~WE.RAM6: RCON1.7, U1.76 (~WE.RAM6)
/~WE.RAM7: RCON2.17, U1.77 (~WE.RAM7)
/~WE.RAM8: RCON1.14, U1.78 (~WE.RAM8)
/~WE.U2: CON1.24, U2.26 (~WE)
/~WP.U2: CON1.28, R4.1, U2.37 (~WP)
/~WRAM: CN1.32 (/WRAM), CN2.32 (/WRAM)
/~Write.Sys: CN1.54 (/Write), CN2.54 (/Write), R27.2, U1.27 (~WRITE.SNES), U2.2 (~WR), U5.27 (~WE), U6.27 (~WE), U7.27 (~WE)
unnamed: CON1.5, CON1.7, CON1.9, CON1.11, JP1.2
unnamed: C12.1, D1.2 (A), EC2.1, R18.2, U1.46 (Unknown)
unnamed: R20.1, R21.1, U1.34 (SNES.Pwr_Detect)
unnamed: R26.1, R27.1, U5.23 (R/~W)

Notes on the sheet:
R22 - R25 0 Ohm
A B Y __________ L L H L H H H L H H H L

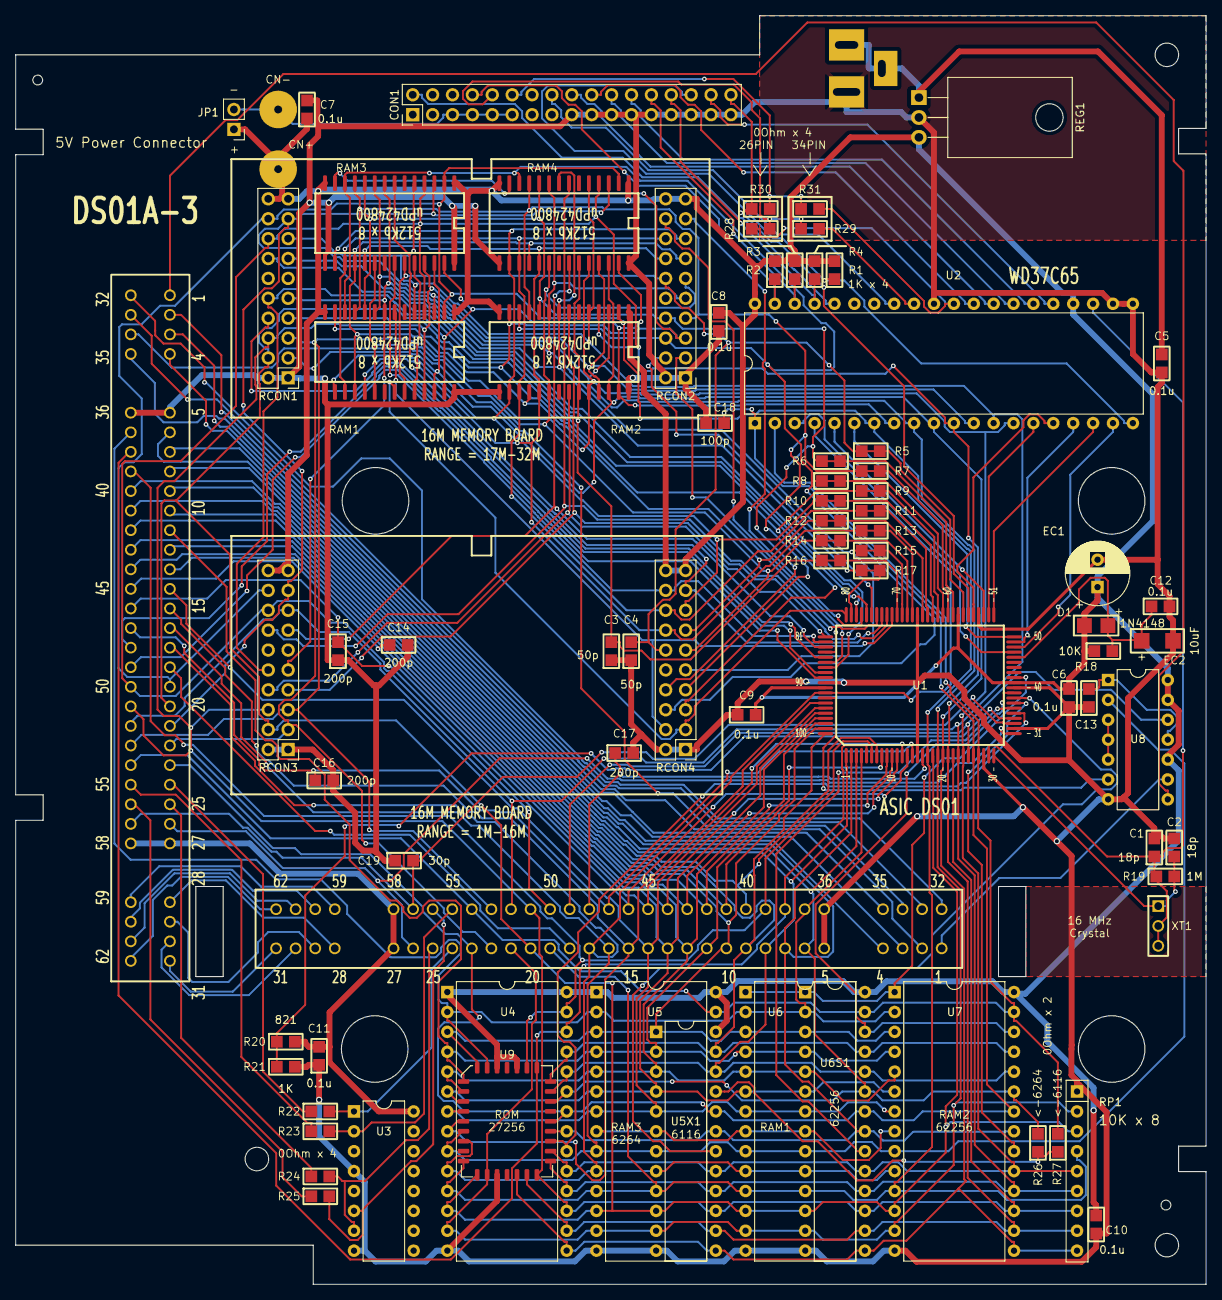
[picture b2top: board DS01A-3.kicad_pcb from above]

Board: 2 copper layers, 152.0 x 162.0 mm, 80 parts (0 on the bottom side), 137 nets.

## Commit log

2024-10-13 Update README.md
    Memory Addon Board updated to include 100 pF capacitors on the CAS lines for stability. Memory addon board is unstable without these capacitors. Old boards can add external caps with no issues.
